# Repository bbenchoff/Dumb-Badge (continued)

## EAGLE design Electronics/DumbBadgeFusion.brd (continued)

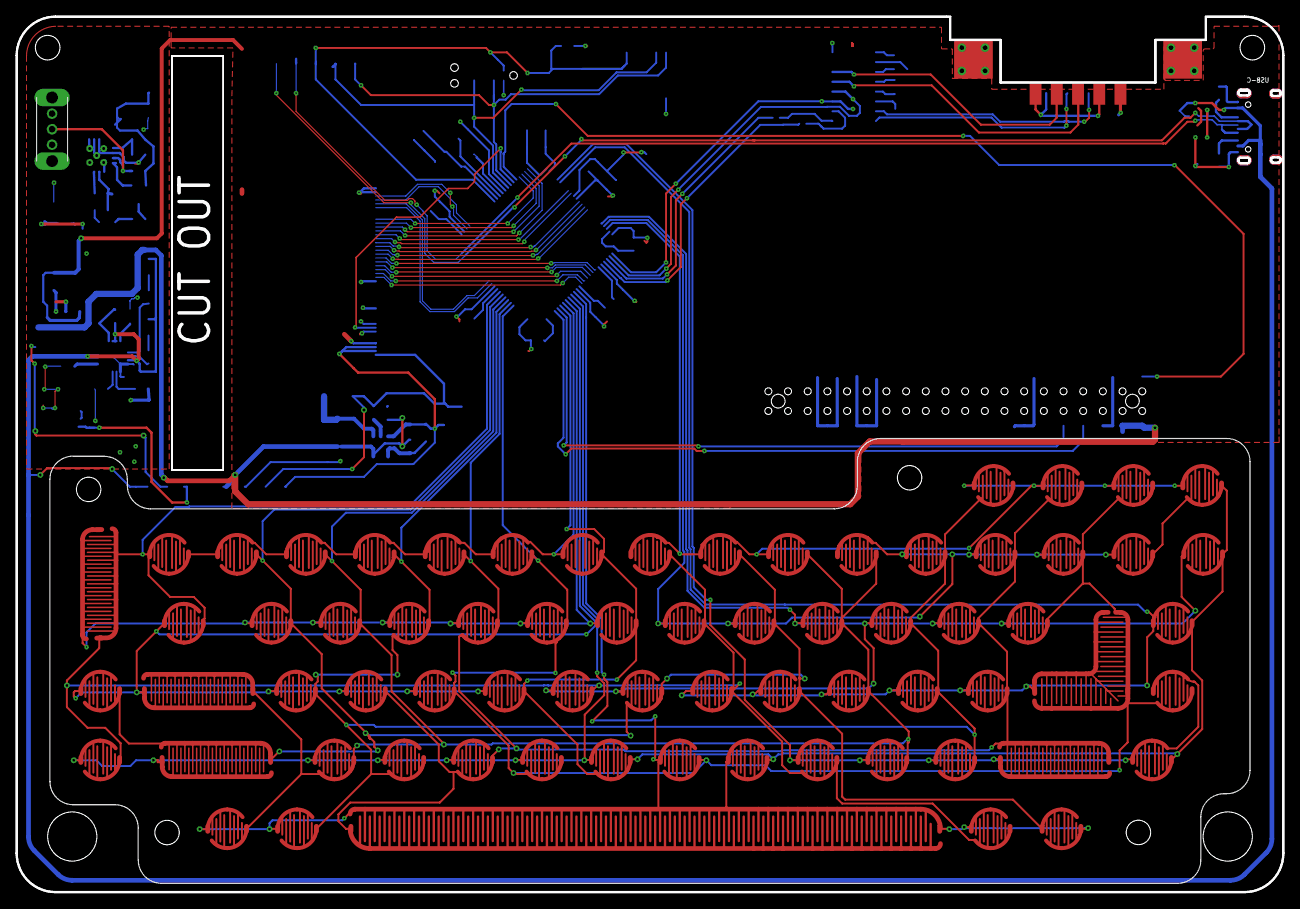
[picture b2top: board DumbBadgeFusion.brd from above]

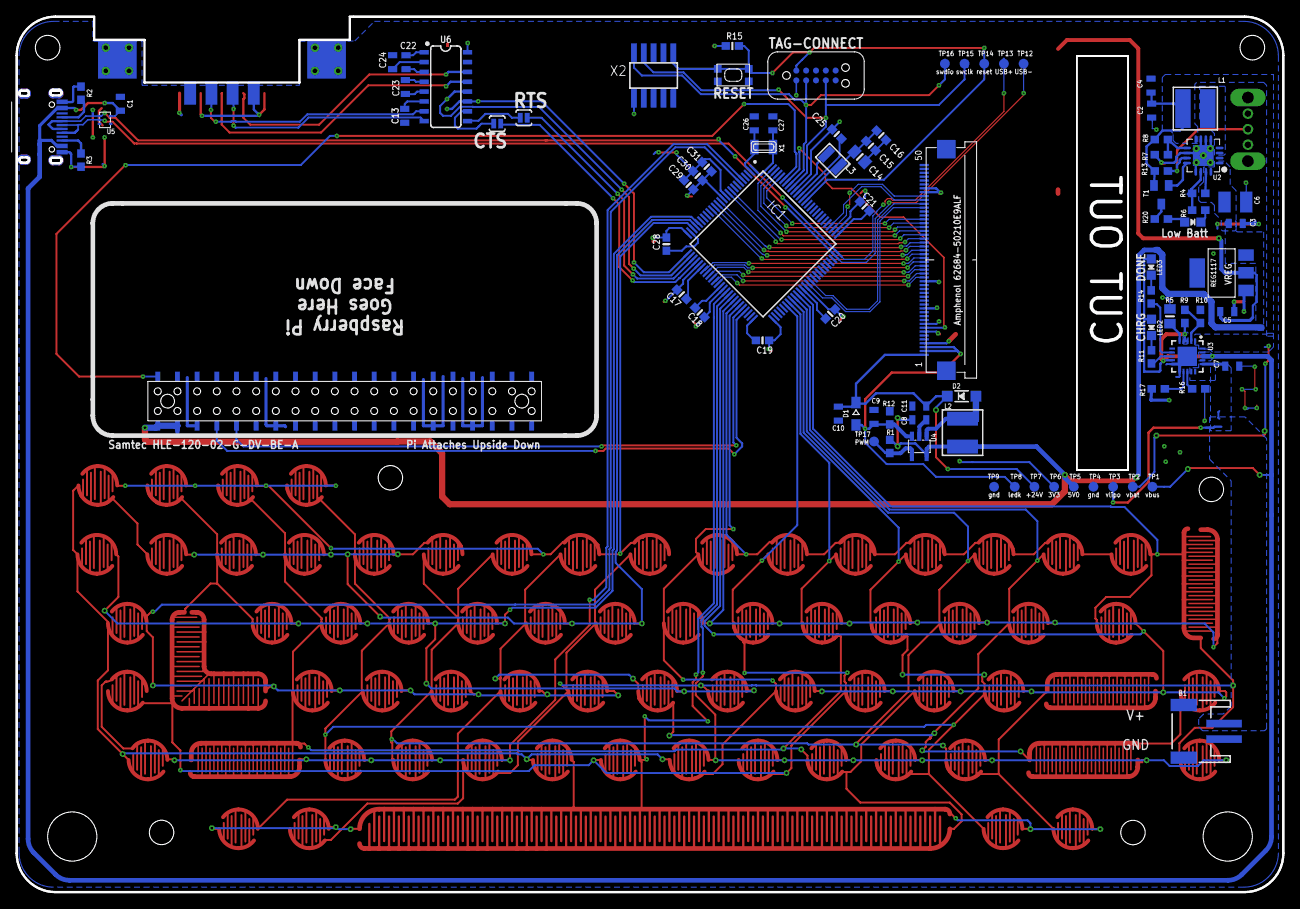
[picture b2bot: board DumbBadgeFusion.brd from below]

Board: 2 copper layers, 163.5 x 113.0 mm, 160 parts (89 on the bottom side), 94 nets.

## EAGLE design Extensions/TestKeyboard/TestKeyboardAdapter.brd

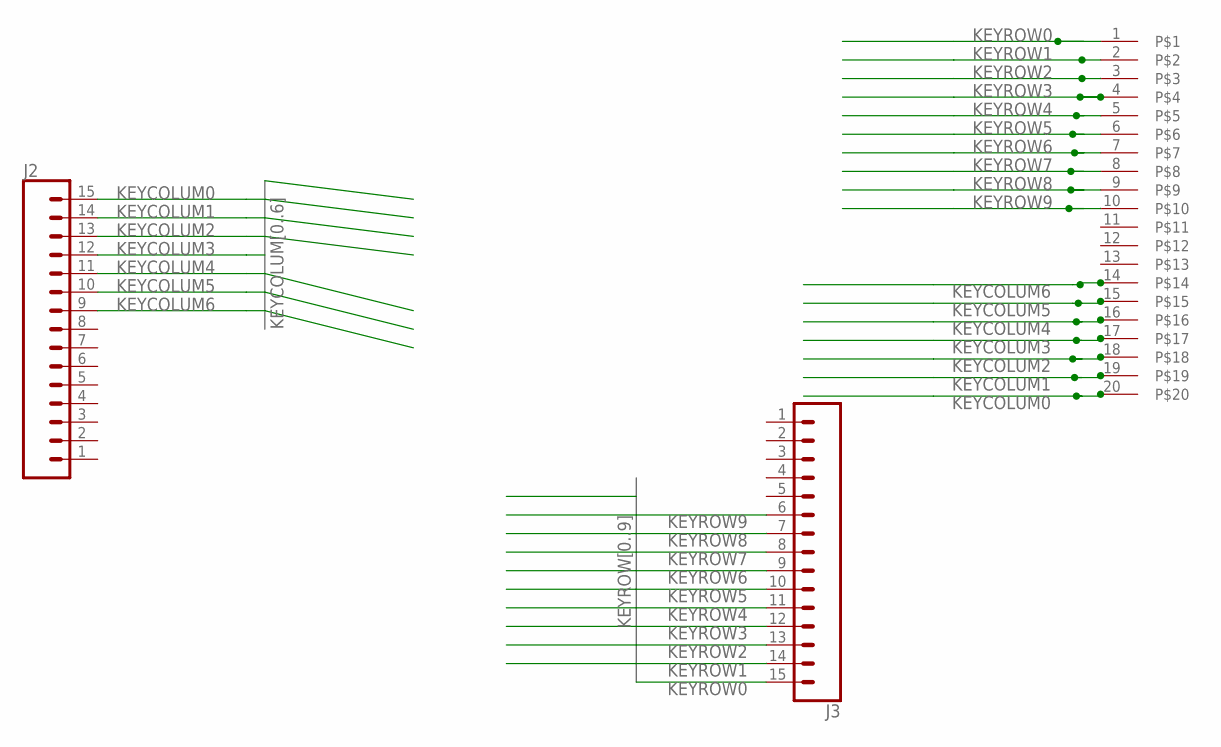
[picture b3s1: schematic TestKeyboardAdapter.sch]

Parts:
J2, J3: CONN_15; 1X15
U$1: FC1-20-L2-T-WT20PIN; FC1-20-L2-T-WT

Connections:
KEYCOLUM0: J2.15, U$1.20
KEYCOLUM1: J2.14, U$1.19
KEYCOLUM2: J2.13, U$1.18
KEYCOLUM3: J2.12, U$1.17
KEYCOLUM4: J2.11, U$1.16
KEYCOLUM5: J2.10, U$1.15
KEYCOLUM6: J2.9, U$1.14
KEYROW0: J3.15, U$1.1
KEYROW1: J3.14, U$1.2
KEYROW2: J3.13, U$1.3
KEYROW3: J3.12, U$1.4
KEYROW4: J3.11, U$1.5
KEYROW5: J3.10, U$1.6
KEYROW6: J3.9, U$1.7
KEYROW7: J3.8, U$1.8
KEYROW8: J3.7, U$1.9
KEYROW9: J3.6, U$1.10

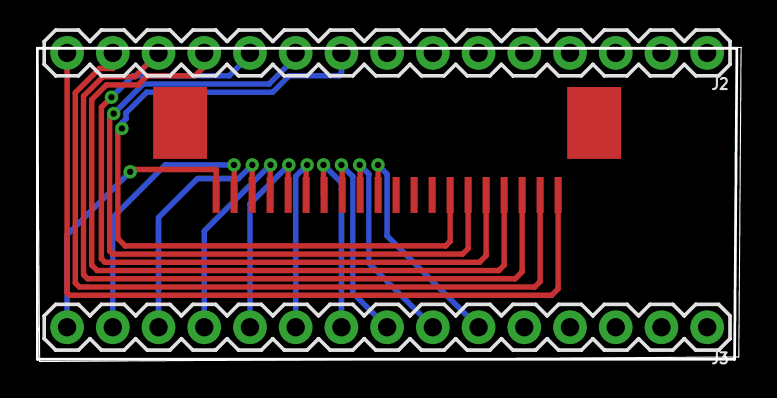
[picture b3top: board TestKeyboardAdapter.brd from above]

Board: 2 copper layers, 39.1 x 17.4 mm, 3 parts (0 on the bottom side), 17 nets.

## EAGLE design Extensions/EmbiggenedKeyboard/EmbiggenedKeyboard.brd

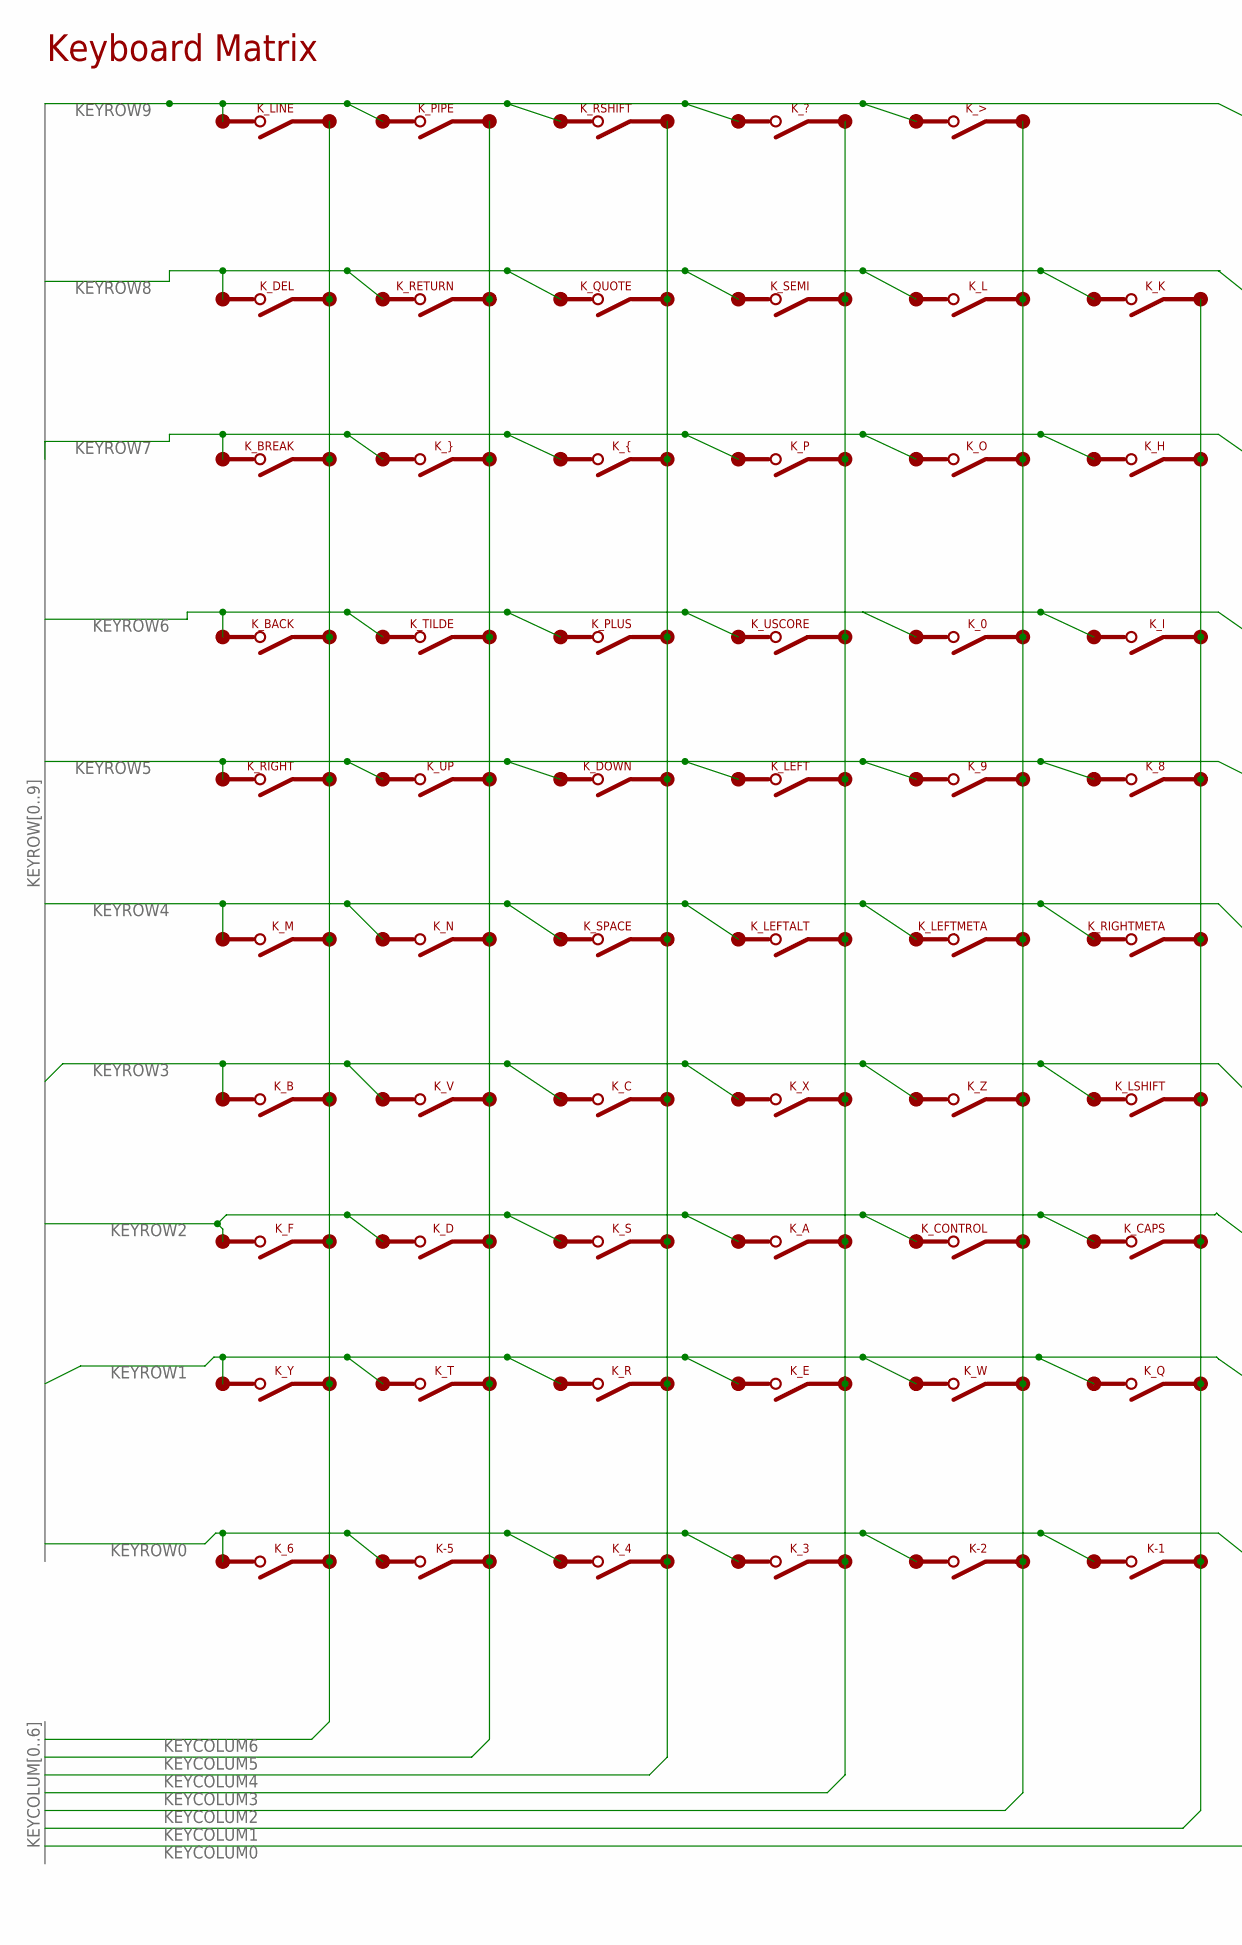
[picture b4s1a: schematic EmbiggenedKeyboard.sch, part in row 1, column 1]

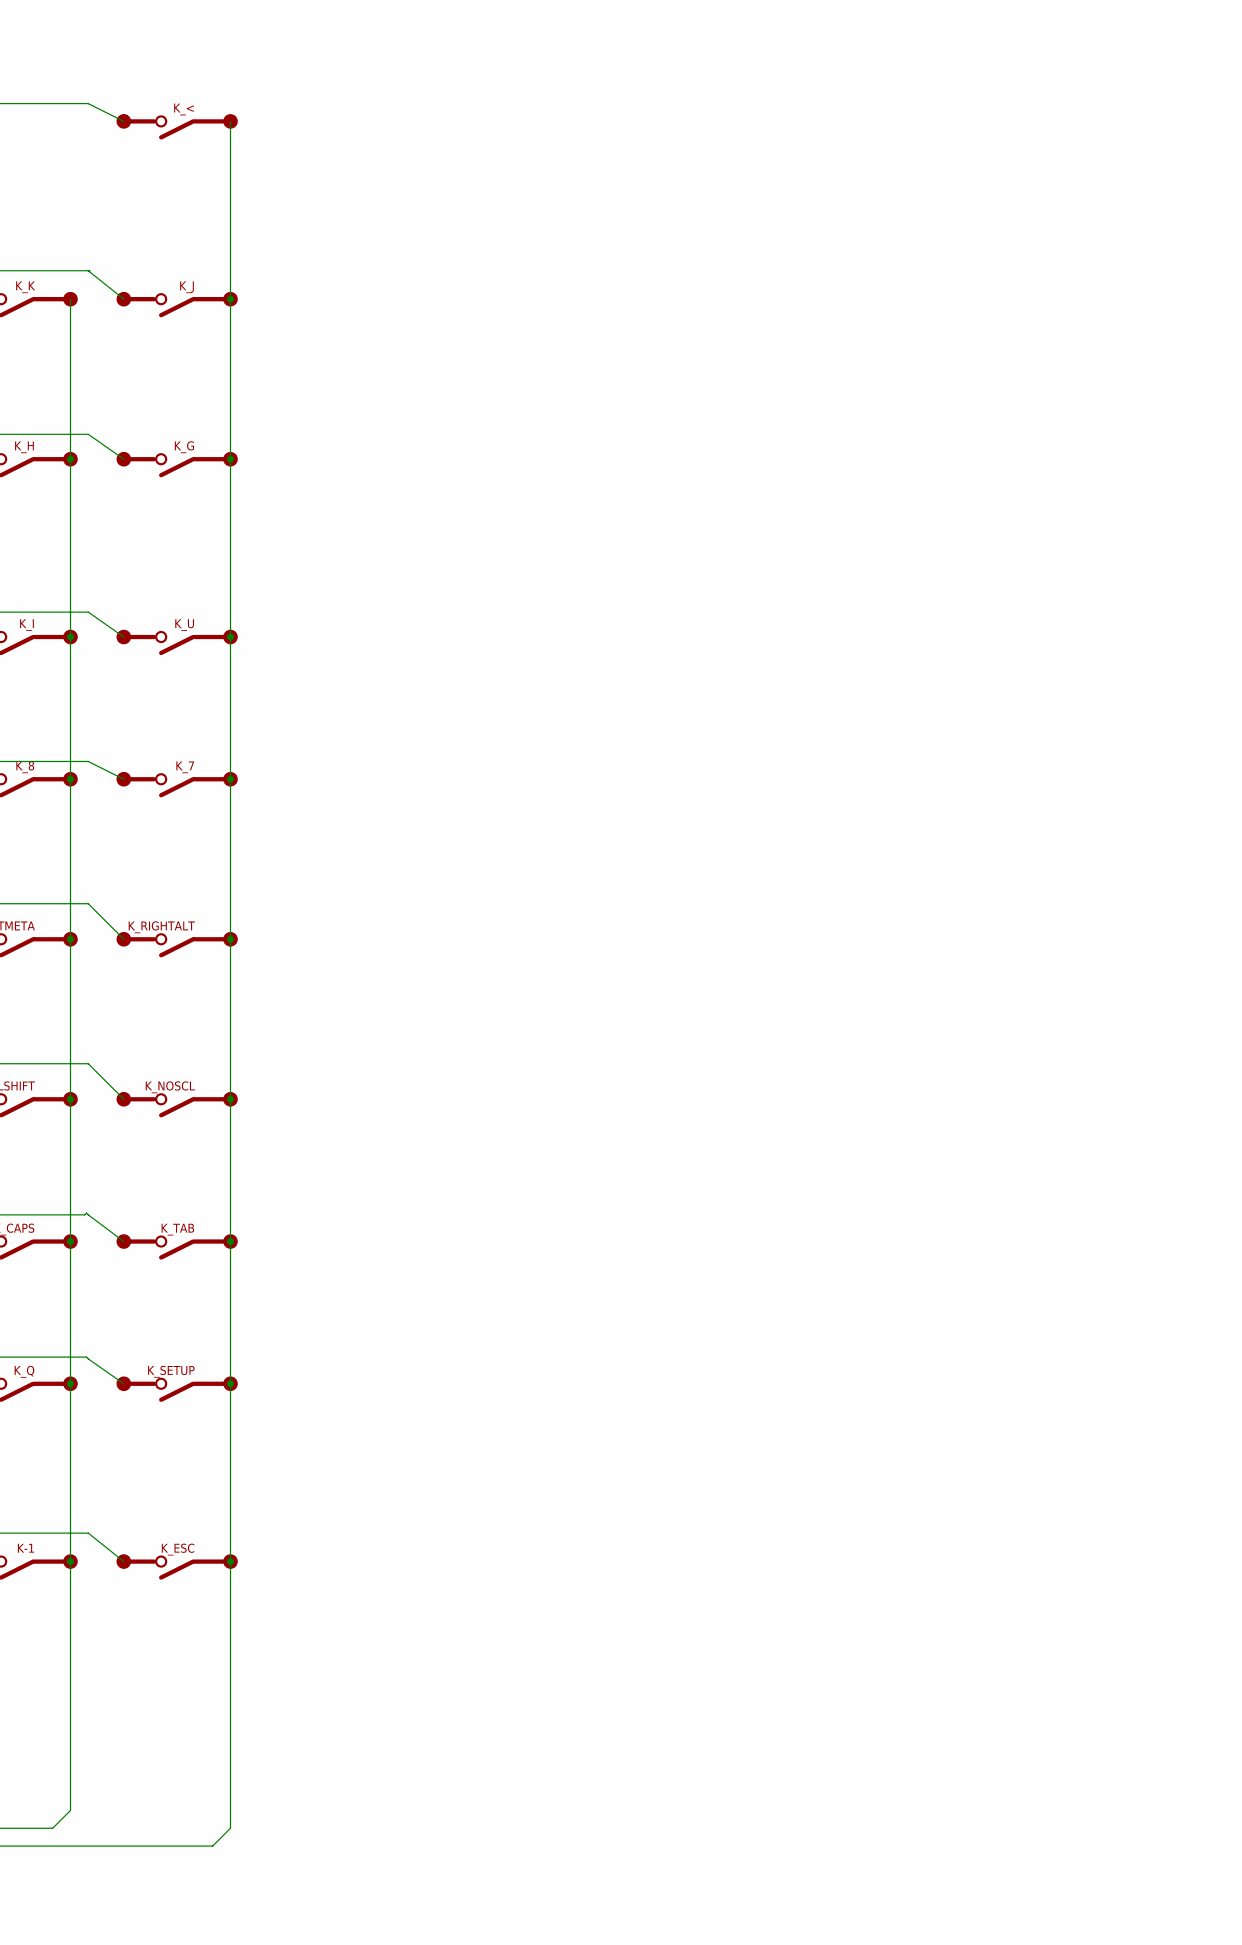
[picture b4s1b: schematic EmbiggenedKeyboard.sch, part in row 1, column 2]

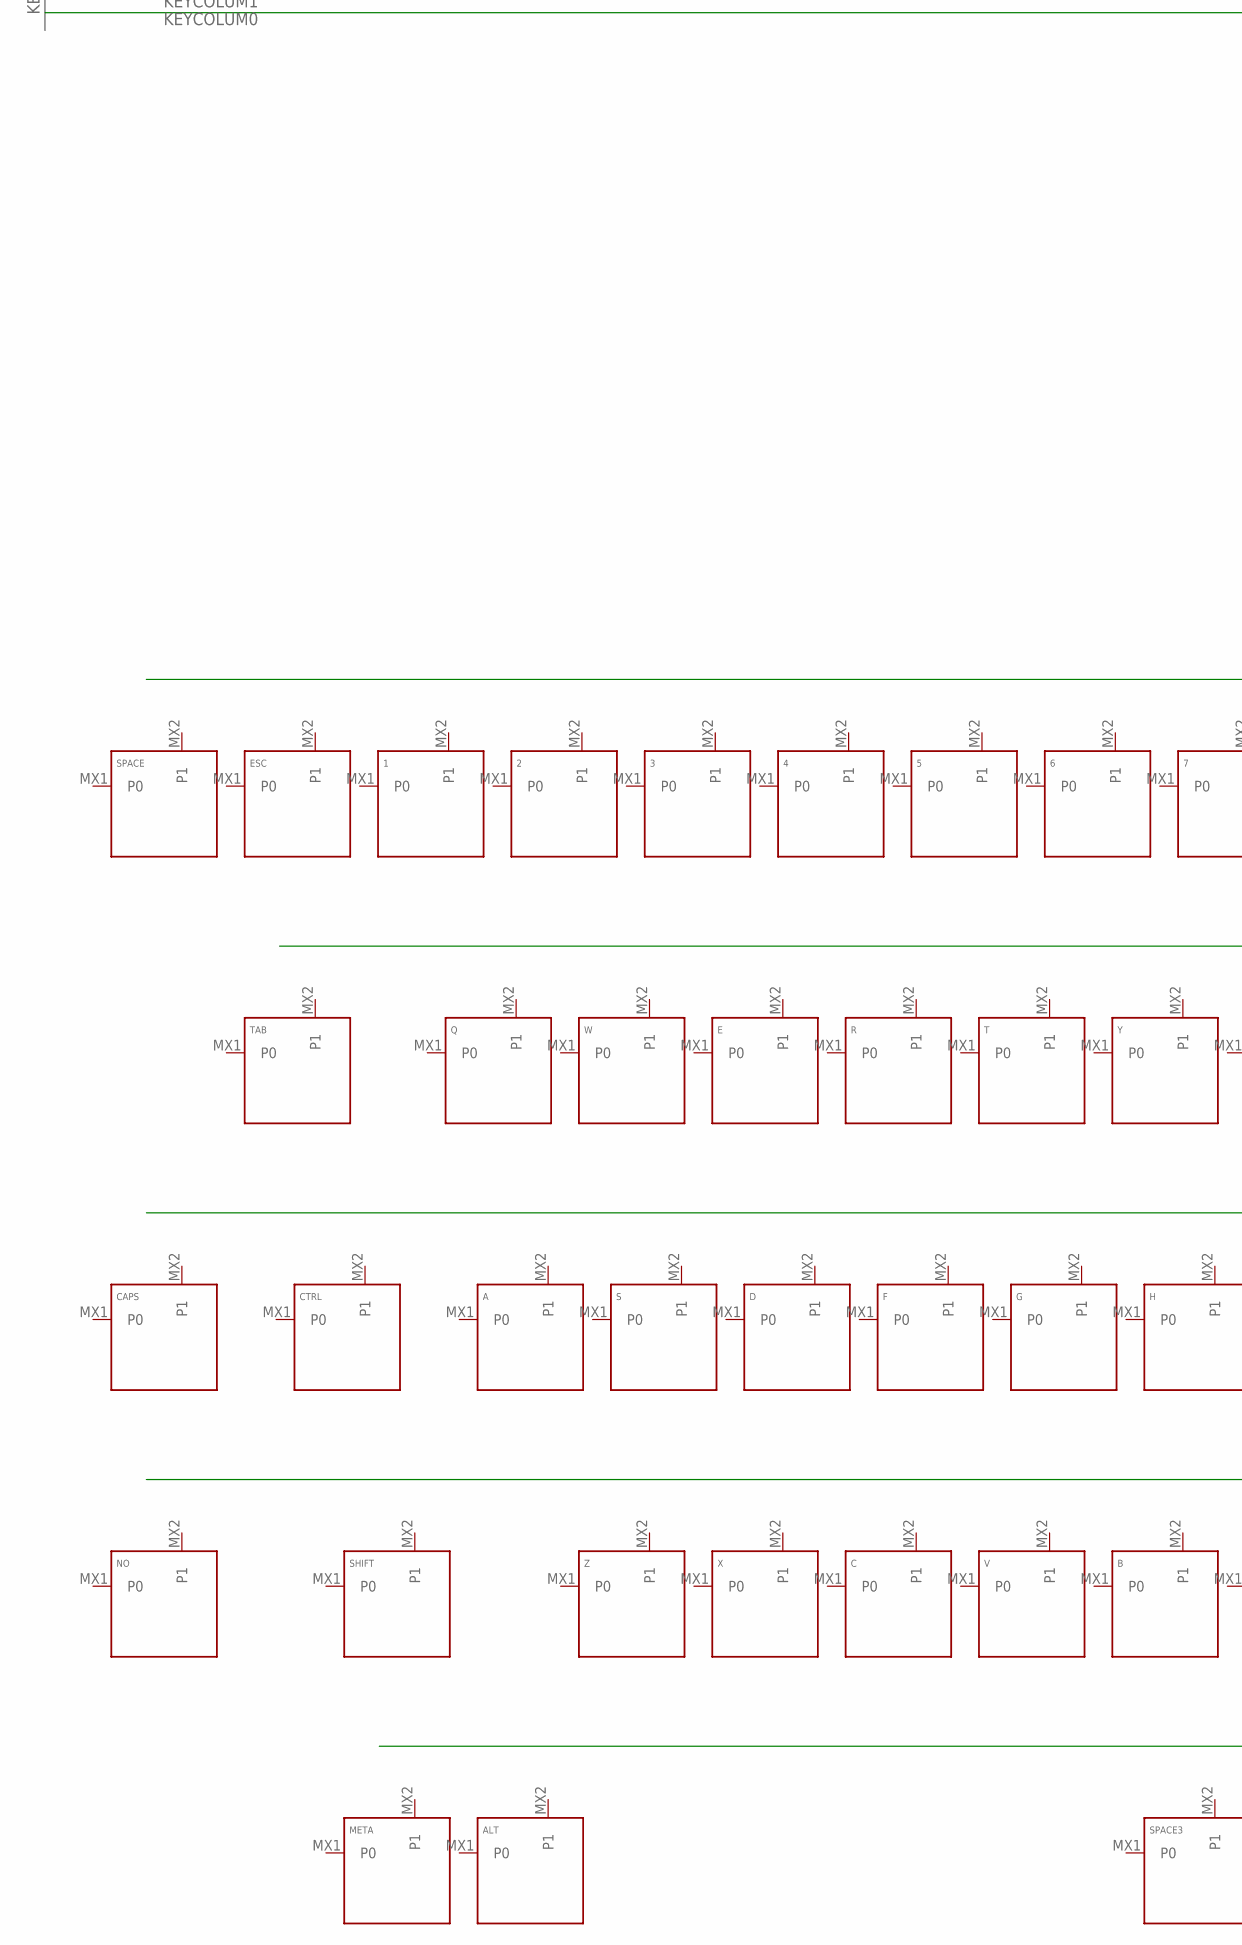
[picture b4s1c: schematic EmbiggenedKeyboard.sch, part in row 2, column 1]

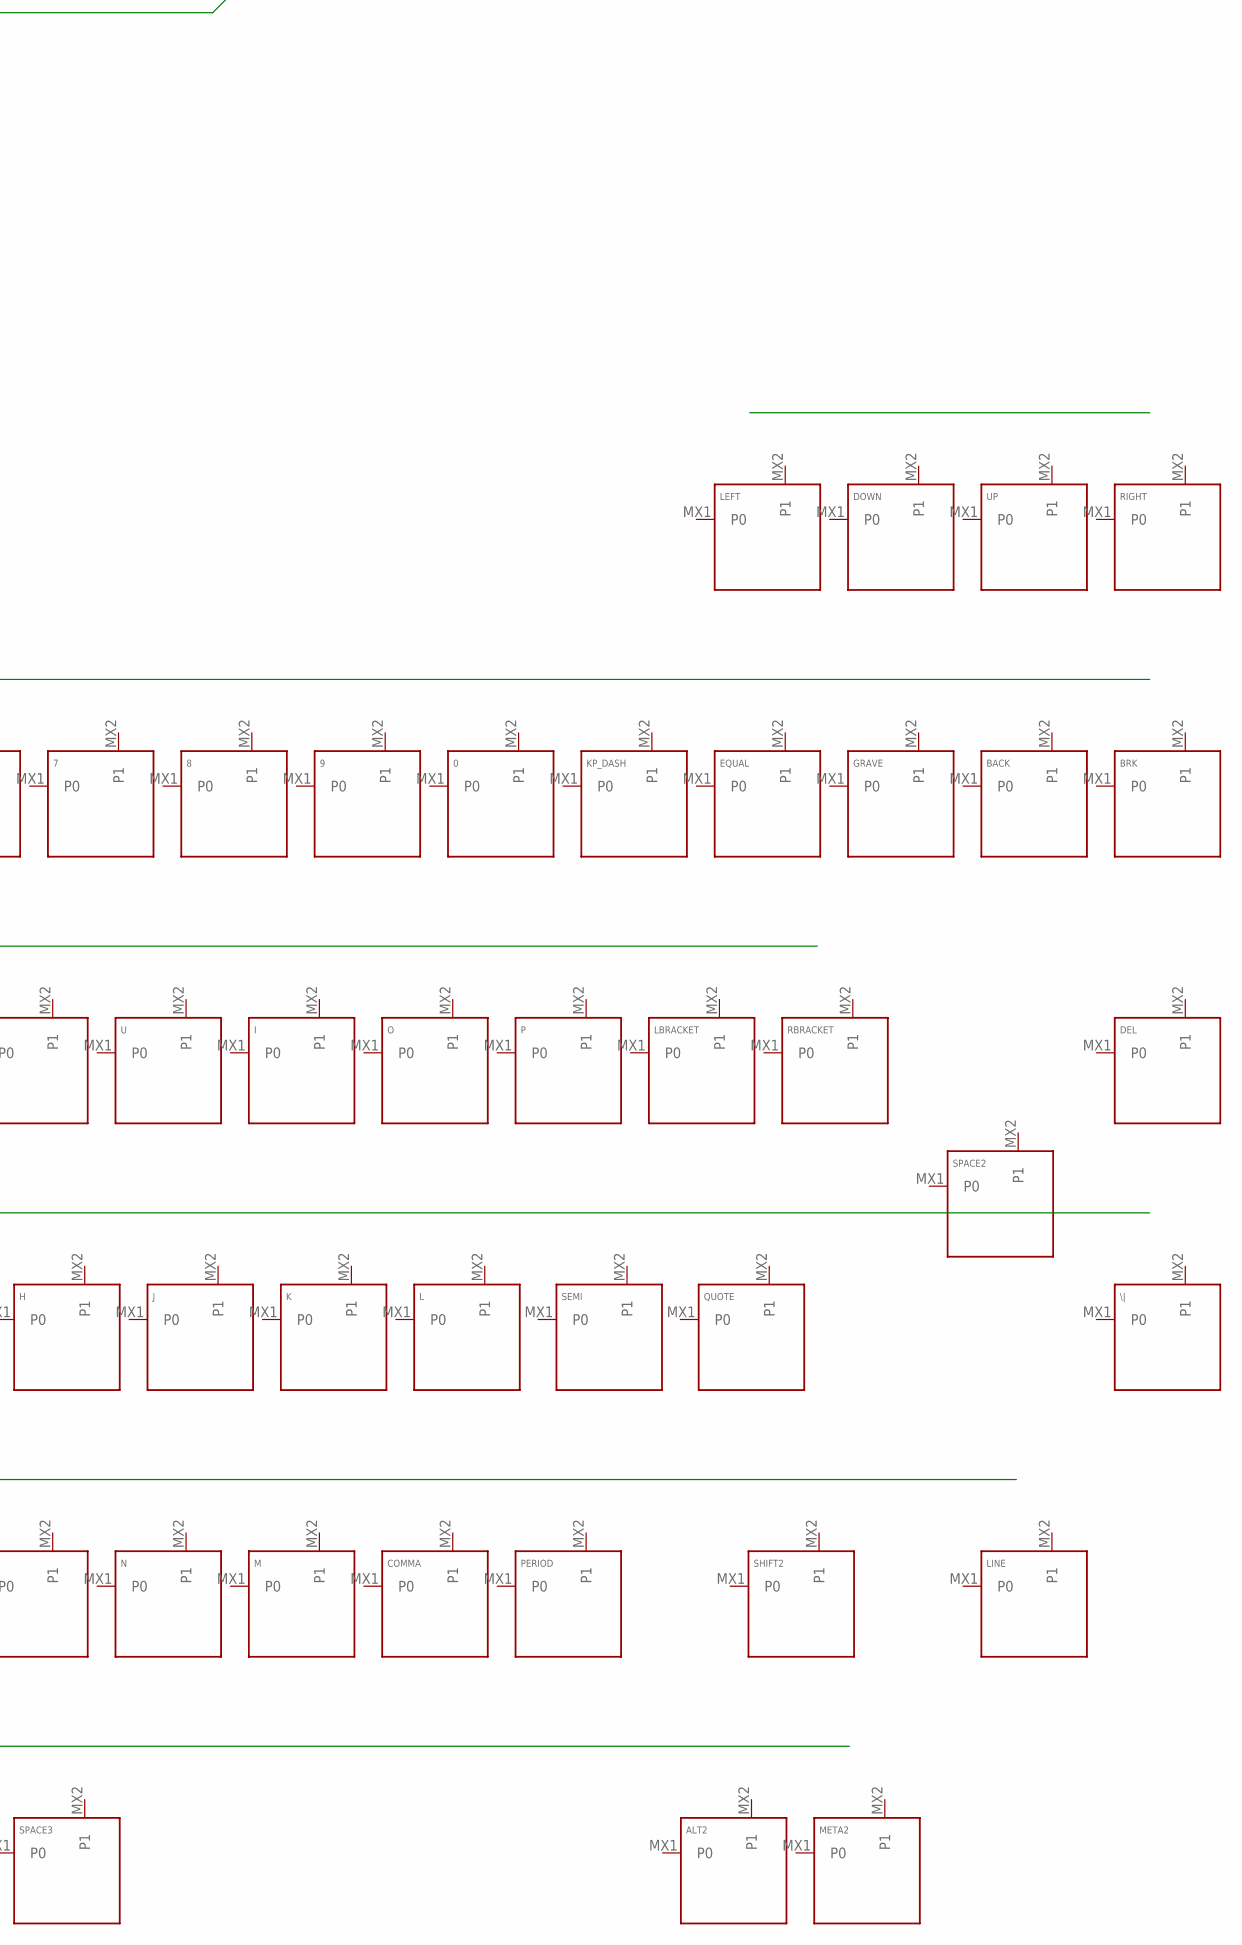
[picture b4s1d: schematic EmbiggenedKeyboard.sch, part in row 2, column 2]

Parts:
0, 1, 2, 3, 4, 5, 6, 7, 8, 9: KEYSWITCH-PLAIN-MX-1U; MX-1U
A: KEYSWITCH-PLAIN-MX-1U; MX-1U
ALT, ALT2: KEYSWITCH-PLAIN-MX-1U; MX-1U
B: KEYSWITCH-PLAIN-MX-1U; MX-1U
BACK: KEYSWITCH-PLAIN-MX-1U; MX-1U
BRK: KEYSWITCH-PLAIN-MX-1U; MX-1U
C: KEYSWITCH-PLAIN-MX-1U; MX-1U
CAPS: KEYSWITCH-PLAIN-MX-1U; MX-1U
COMMA: KEYSWITCH-PLAIN-MX-1U; MX-1U
CTRL: KEYSWITCH-PLAIN-MX-1U; MX-1U
D: KEYSWITCH-PLAIN-MX-1U; MX-1U
DEL: KEYSWITCH-PLAIN-MX-1U; MX-1U
DOWN: KEYSWITCH-PLAIN-MX-1U; MX-1U
E: KEYSWITCH-PLAIN-MX-1U; MX-1U
EQUAL: KEYSWITCH-PLAIN-MX-1U; MX-1U
ESC: KEYSWITCH-PLAIN-MX-1U; MX-1U
F: KEYSWITCH-PLAIN-MX-1U; MX-1U
G: KEYSWITCH-PLAIN-MX-1U; MX-1U
GRAVE: KEYSWITCH-PLAIN-MX-1U; MX-1U
H: KEYSWITCH-PLAIN-MX-1U; MX-1U
I: KEYSWITCH-PLAIN-MX-1U; MX-1U
J: KEYSWITCH-PLAIN-MX-1U; MX-1U
K: KEYSWITCH-PLAIN-MX-1U; MX-1U
K-1, K-2, K-5: 1U_PAD; SILICONE_SWITCH
KP_DASH: KEYSWITCH-PLAIN-MX-1U; MX-1U
K_0, K_3, K_4, K_6, K_7, K_8, K_9: 1U_PAD; SILICONE_SWITCH
K_<: 1U_PAD; SILICONE_SWITCH
K_>: 1U_PAD; SILICONE_SWITCH
K_?: 1U_PAD; SILICONE_SWITCH
K_A: 1U_PAD; SILICONE_SWITCH
K_B: 1U_PAD; SILICONE_SWITCH
K_BACK: 1U_PAD; SILICONE_SWITCH
K_BREAK: 1U_PAD; SILICONE_SWITCH
K_C: 1U_PAD; SILICONE_SWITCH
K_CAPS: 1U_PAD; SILICONE_SWITCH
K_CONTROL: 2U_PAD; SILICONE_SWITCH_2U
K_D: 1U_PAD; SILICONE_SWITCH
K_DEL: 1U_PAD; SILICONE_SWITCH
K_DOWN: 1U_PAD; SILICONE_SWITCH
K_E: 1U_PAD; SILICONE_SWITCH
K_ESC: 1U_PAD; SILICONE_SWITCH
K_F: 1U_PAD; SILICONE_SWITCH
K_G: 1U_PAD; SILICONE_SWITCH
K_H: 1U_PAD; SILICONE_SWITCH
K_I: 1U_PAD; SILICONE_SWITCH
K_J: 1U_PAD; SILICONE_SWITCH
K_K: 1U_PAD; SILICONE_SWITCH
K_L: 1U_PAD; SILICONE_SWITCH
K_LEFT: 1U_PAD; SILICONE_SWITCH
K_LEFTALT: 1U_PAD; SILICONE_SWITCH
K_LEFTMETA: 1U_PAD; SILICONE_SWITCH
K_LINE: 1U_PAD; SILICONE_SWITCH
K_LSHIFT: 2U_PAD; SILICONE_SWITCH_2U
K_M: 1U_PAD; SILICONE_SWITCH
K_N: 1U_PAD; SILICONE_SWITCH
K_NOSCL: 1U_PAD; SILICONE_SWITCH
K_O: 1U_PAD; SILICONE_SWITCH
K_P: 1U_PAD; SILICONE_SWITCH
K_PIPE: 1U_PAD; SILICONE_SWITCH
K_PLUS: 1U_PAD; SILICONE_SWITCH
K_Q: 1U_PAD; SILICONE_SWITCH
K_QUOTE: 1U_PAD; SILICONE_SWITCH
K_R: 1U_PAD; SILICONE_SWITCH
K_RETURN: RETURN_PAD; SILICONE_RETURN
K_RIGHT: 1U_PAD; SILICONE_SWITCH
K_RIGHTALT: 1U_PAD; SILICONE_SWITCH
K_RIGHTMETA: 1U_PAD; SILICONE_SWITCH
K_RSHIFT: 2U_PAD; SILICONE_SWITCH_2U
K_S: 1U_PAD; SILICONE_SWITCH
K_SEMI: 1U_PAD; SILICONE_SWITCH
K_SETUP: 2U_PAD; SILICONE_SWITCH_2U
K_SPACE: SPACE_PAD; SILICONE_SPACE
K_T: 1U_PAD; SILICONE_SWITCH
K_TAB: 1U_PAD; SILICONE_SWITCH
K_TILDE: 1U_PAD; SILICONE_SWITCH
K_U: 1U_PAD; SILICONE_SWITCH
K_UP: 1U_PAD; SILICONE_SWITCH
K_USCORE: 1U_PAD; SILICONE_SWITCH
K_V: 1U_PAD; SILICONE_SWITCH
K_W: 1U_PAD; SILICONE_SWITCH
K_X: 1U_PAD; SILICONE_SWITCH
K_Y: 1U_PAD; SILICONE_SWITCH
K_Z: 1U_PAD; SILICONE_SWITCH
K_{: 1U_PAD; SILICONE_SWITCH
K_}: 1U_PAD; SILICONE_SWITCH
L: KEYSWITCH-PLAIN-MX-1U; MX-1U
LBRACKET: KEYSWITCH-PLAIN-MX-1U; MX-1U
LEFT: KEYSWITCH-PLAIN-MX-1U; MX-1U
LINE: KEYSWITCH-PLAIN-MX-1U; MX-1U
M: KEYSWITCH-PLAIN-MX-1U; MX-1U
META, META2: KEYSWITCH-PLAIN-MX-1U; MX-1U
N: KEYSWITCH-PLAIN-MX-1U; MX-1U
NO: KEYSWITCH-PLAIN-MX-1U; MX-1U
O: KEYSWITCH-PLAIN-MX-1U; MX-1U
P: KEYSWITCH-PLAIN-MX-1U; MX-1U
PERIOD: KEYSWITCH-PLAIN-MX-1U; MX-1U
Q: KEYSWITCH-PLAIN-MX-1U; MX-1U
QUOTE: KEYSWITCH-PLAIN-MX-1U; MX-1U
R: KEYSWITCH-PLAIN-MX-1U; MX-1U
RBRACKET: KEYSWITCH-PLAIN-MX-1U; MX-1U
RIGHT: KEYSWITCH-PLAIN-MX-1U; MX-1U
S: KEYSWITCH-PLAIN-MX-1U; MX-1U
SEMI: KEYSWITCH-PLAIN-MX-1U; MX-1U
SHIFT, SHIFT2: KEYSWITCH-PLAIN-MX-1U; MX-1U
SPACE, SPACE2, SPACE3: KEYSWITCH-PLAIN-MX-1U; MX-1U
T: KEYSWITCH-PLAIN-MX-1U; MX-1U
TAB: KEYSWITCH-PLAIN-MX-1U; MX-1U
U: KEYSWITCH-PLAIN-MX-1U; MX-1U
UP: KEYSWITCH-PLAIN-MX-1U; MX-1U
V: KEYSWITCH-PLAIN-MX-1U; MX-1U
W: KEYSWITCH-PLAIN-MX-1U; MX-1U
X: KEYSWITCH-PLAIN-MX-1U; MX-1U
Y: KEYSWITCH-PLAIN-MX-1U; MX-1U
Z: KEYSWITCH-PLAIN-MX-1U; MX-1U
\|: KEYSWITCH-PLAIN-MX-1U; MX-1U

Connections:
KEYCOLUM0: K_7.P$2, K_<.P$2, K_ESC.P$2, K_G.P$2, K_J.P$2, K_NOSCL.P$2, K_RIGHTALT.P$2, K_SETUP.P$2, K_TAB.P$2, K_U.P$2
KEYCOLUM1: K-1.P$2, K_8.P$2, K_CAPS.P$2, K_H.P$2, K_I.P$2, K_K.P$2, K_LSHIFT.P$2, K_Q.P$2, K_RIGHTMETA.P$2
KEYCOLUM2: K-2.P$2, K_0.P$2, K_9.P$2, K_>.P$2, K_CONTROL.P$2, K_L.P$2, K_LEFTMETA.P$2, K_O.P$2, K_W.P$2, K_Z.P$2
KEYCOLUM3: K_3.P$2, K_?.P$2, K_A.P$2, K_E.P$2, K_LEFT.P$2, K_LEFTALT.P$2, K_P.P$2, K_SEMI.P$2, K_USCORE.P$2, K_X.P$2
KEYCOLUM4: K_4.P$2, K_C.P$2, K_DOWN.P$2, K_PLUS.P$2, K_QUOTE.P$2, K_R.P$2, K_RSHIFT.P$2, K_S.P$2, K_SPACE.P$2, K_{.P$2
KEYCOLUM5: K-5.P$2, K_D.P$2, K_N.P$2, K_PIPE.P$2, K_RETURN.P$2, K_T.P$2, K_TILDE.P$2, K_UP.P$2, K_V.P$2, K_}.P$2
KEYCOLUM6: K_6.P$2, K_B.P$2, K_BACK.P$2, K_BREAK.P$2, K_DEL.P$2, K_F.P$2, K_LINE.P$2, K_M.P$2, K_RIGHT.P$2, K_Y.P$2
KEYROW0: K-1.P$1, K-2.P$1, K-5.P$1, K_3.P$1, K_4.P$1, K_6.P$1, K_ESC.P$1
KEYROW1: K_E.P$1, K_Q.P$1, K_R.P$1, K_SETUP.P$1, K_T.P$1, K_W.P$1, K_Y.P$1
KEYROW2: K_A.P$1, K_CAPS.P$1, K_CONTROL.P$1, K_D.P$1, K_F.P$1, K_S.P$1, K_TAB.P$1
KEYROW3: K_B.P$1, K_C.P$1, K_LSHIFT.P$1, K_NOSCL.P$1, K_V.P$1, K_X.P$1, K_Z.P$1
KEYROW4: K_LEFTALT.P$1, K_LEFTMETA.P$1, K_M.P$1, K_N.P$1, K_RIGHTALT.P$1, K_RIGHTMETA.P$1, K_SPACE.P$1
KEYROW5: K_7.P$1, K_8.P$1, K_9.P$1, K_DOWN.P$1, K_LEFT.P$1, K_RIGHT.P$1, K_UP.P$1
KEYROW6: K_0.P$1, K_BACK.P$1, K_I.P$1, K_PLUS.P$1, K_TILDE.P$1, K_U.P$1, K_USCORE.P$1
KEYROW7: K_BREAK.P$1, K_G.P$1, K_H.P$1, K_O.P$1, K_P.P$1, K_{.P$1, K_}.P$1
KEYROW8: K_DEL.P$1, K_J.P$1, K_K.P$1, K_L.P$1, K_QUOTE.P$1, K_RETURN.P$1, K_SEMI.P$1
KEYROW9: K_<.P$1, K_>.P$1, K_?.P$1, K_LINE.P$1, K_PIPE.P$1, K_RSHIFT.P$1

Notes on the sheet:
Keyboard Matrix

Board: 2 copper layers, 137 parts (0 on the bottom side), 17 nets, no tracks yet.

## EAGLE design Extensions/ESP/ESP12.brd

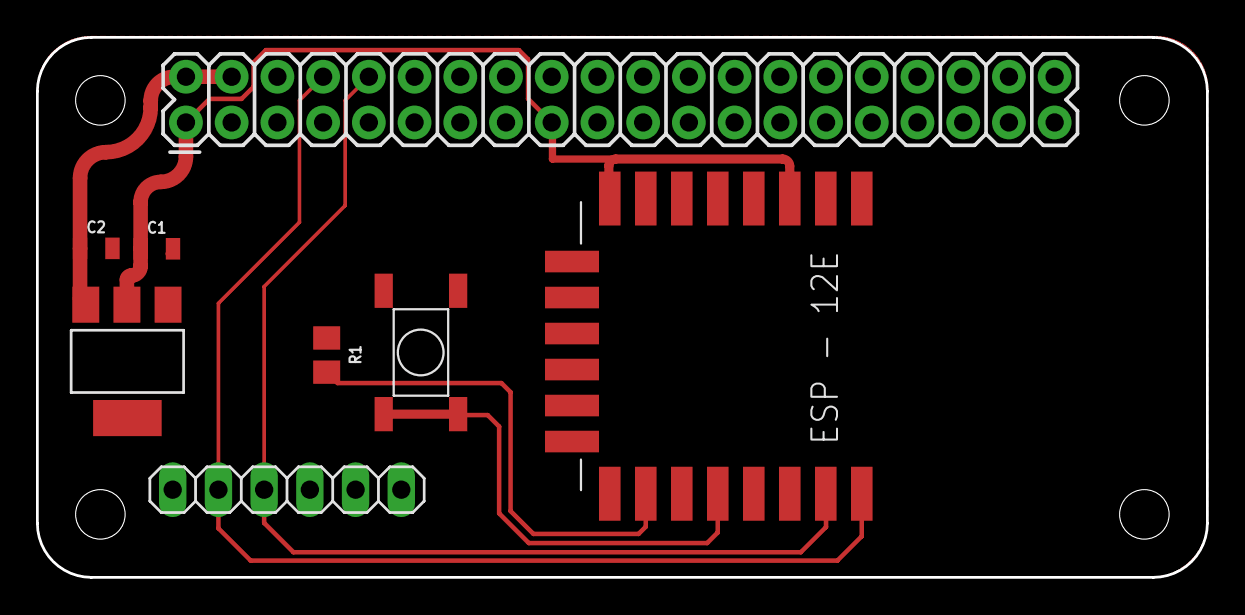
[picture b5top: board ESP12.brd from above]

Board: 2 copper layers, 65.0 x 30.0 mm, 8 parts (0 on the bottom side), 7 nets.

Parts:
C1, C2: 10uF; 0805
FLASH: MOMENTARYSW; SWITCHMOMENTARY
IC1: REG1117; SOT223
J1: RASPBERRYPI-40-PIN-GPIO_PTH_NO_SHROUD; 2X20
JP2: 1X06
R1: 10k; R0805
U3: ESP12E-SMD

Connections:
5V: C2.1, IC1.3, J1.2, J1.4
FTDI_RX: J1.8, JP2.5, U3.TXD0
FTDI_TX: J1.10, JP2.4, U3.RXD0
GND: C1.2, C2.2, FLASH.R1, FLASH.R2, IC1.1, J1.6, J1.9, J1.14, J1.20, J1.25, J1.30, J1.34, J1.39, JP2.1, R1.1, U3.GND
unnamed: R1.2, U3.GPIO15
unnamed: FLASH.L1, FLASH.L2, U3.GPIO0
VCC: C1.1, IC1.2, J1.1, J1.17, U3.CH_PD, U3.VCC

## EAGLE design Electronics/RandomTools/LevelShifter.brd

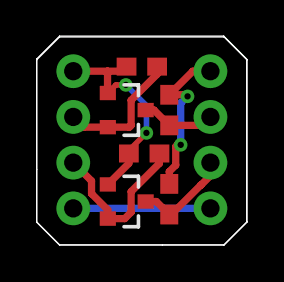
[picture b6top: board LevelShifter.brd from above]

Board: 2 copper layers, 11.7 x 11.6 mm, 8 parts (0 on the bottom side), 7 nets.

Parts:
J1, J2: 1X04_NO_SILK
Q1, Q2: 220mA/50V/3.5Ω; SOT23-3
R1, R2, R3, R4: 10k; 0603

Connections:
GND: J1.1, J2.4
HI1: J2.2, Q1.3, R3.1
HI2: J2.3, Q2.3, R4.1
HIPW: J2.1, R3.2, R4.2
LOW1: J1.3, Q1.2, R1.1
LOW2: J1.2, Q2.2, R2.1
LOWPW: J1.4, Q1.1, Q2.1, R1.2, R2.2

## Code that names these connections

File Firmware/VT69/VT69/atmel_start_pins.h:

/*
 * Code generated from Atmel Start.
 *
 * This file will be overwritten when reconfiguring your Atmel Start project.
 * Please copy examples or other code you want to keep to a separate file
 * to avoid losing it when reconfiguring.
 */
#ifndef ATMEL_START_PINS_H_INCLUDED
#define ATMEL_START_PINS_H_INCLUDED


// SAMD51 has 14 pin functions

#define GPIO_PIN_FUNCTION_A 0
#define GPIO_PIN_FUNCTION_B 1
#define GPIO_PIN_FUNCTION_C 2
#define GPIO_PIN_FUNCTION_D 3
#define GPIO_PIN_FUNCTION_E 4
#define GPIO_PIN_FUNCTION_F 5
#define GPIO_PIN_FUNCTION_G 6
#define GPIO_PIN_FUNCTION_H 7
#define GPIO_PIN_FUNCTION_I 8
#define GPIO_PIN_FUNCTION_J 9
#define GPIO_PIN_FUNCTION_K 10
#define GPIO_PIN_FUNCTION_L 11
#define GPIO_PIN_FUNCTION_M 12
#define GPIO_PIN_FUNCTION_N 13

#define PA00 GPIO(GPIO_PORTA, 0)
#define PA01 GPIO(GPIO_PORTA, 1)
#define PA02 GPIO(GPIO_PORTA, 2)
#define PA03 GPIO(GPIO_PORTA, 3)
#define PA04 GPIO(GPIO_PORTA, 4)
#define PA05 GPIO(GPIO_PORTA, 5)
#define PA06 GPIO(GPIO_PORTA, 6)
#define PA07 GPIO(GPIO_PORTA, 7)
#define PA08 GPIO(GPIO_PORTA, 8)
#define PA09 GPIO(GPIO_PORTA, 9)
#define PA10 GPIO(GPIO_PORTA, 10)
#define PA11 GPIO(GPIO_PORTA, 11)
#define PA12 GPIO(GPIO_PORTA, 12)
#define PA13 GPIO(GPIO_PORTA, 13)
#define PA14 GPIO(GPIO_PORTA, 14)
#define PA15 GPIO(GPIO_PORTA, 15)
#define PA16 GPIO(GPIO_PORTA, 16)
#define PA17 GPIO(GPIO_PORTA, 17)
#define PA18 GPIO(GPIO_PORTA, 18)
#define PA19 GPIO(GPIO_PORTA, 19)
#define PA20 GPIO(GPIO_PORTA, 20)
#define PA21 GPIO(GPIO_PORTA, 21)
#define PA22 GPIO(GPIO_PORTA, 22)
#define PA23 GPIO(GPIO_PORTA, 23)
#define PA24 GPIO(GPIO_PORTA, 24)
#define PA25 GPIO(GPIO_PORTA, 25)
#define PA27 GPIO(GPIO_PORTA, 27)
#define PA30 GPIO(GPIO_PORTA, 30)
#define PA31 GPIO(GPIO_PORTA, 31)

#define PB00 GPIO(GPIO_PORTB, 0)
#define PB01 GPIO(GPIO_PORTB, 1)
#define PB02 GPIO(GPIO_PORTB, 2)
#define PB03 GPIO(GPIO_PORTB, 3)
#define PB04 GPIO(GPIO_PORTB, 4)
#define PB05 GPIO(GPIO_PORTB, 5)
#define PB06 GPIO(GPIO_PORTB, 6)
#define PB07 GPIO(GPIO_PORTB, 7)
#define PB08 GPIO(GPIO_PORTB, 8)
#define PB09 GPIO(GPIO_PORTB, 9)
#define PB10 GPIO(GPIO_PORTB, 10)
#define PB11 GPIO(GPIO_PORTB, 11)
#define PB12 GPIO(GPIO_PORTB, 12)
#define PB13 GPIO(GPIO_PORTB, 13)
#define PB14 GPIO(GPIO_PORTB, 14)
#define PB15 GPIO(GPIO_PORTB, 15)
#define PB16 GPIO(GPIO_PORTB, 16)
#define PB17 GPIO(GPIO_PORTB, 17)
#define PB18 GPIO(GPIO_PORTB, 18)
#define PB19 GPIO(GPIO_PORTB, 19)
#define PB20 GPIO(GPIO_PORTB, 20)
#define PB21 GPIO(GPIO_PORTB, 21)
#define PB22 GPIO(GPIO_PORTB, 22)
#define PB23 GPIO(GPIO_PORTB, 23)
#define PB24 GPIO(GPIO_PORTB, 24)
#define PB25 GPIO(GPIO_PORTB, 25)
#define PB30 GPIO(GPIO_PORTB, 30)
#define PB31 GPIO(GPIO_PORTB, 31)

#define PC00 GPIO(GPIO_PORTC, 0)
#define PC01 GPIO(GPIO_PORTC, 1)
#define PC02 GPIO(GPIO_PORTC, 2)
#define PC03 GPIO(GPIO_PORTC, 3)
#define PC05 GPIO(GPIO_PORTC, 5)
#define PC06 GPIO(GPIO_PORTC, 6)
#define PC07 GPIO(GPIO_PORTC, 7)
#define PC10 GPIO(GPIO_PORTC, 10)
#define PC11 GPIO(GPIO_PORTC, 11)
#define PC12 GPIO(GPIO_PORTC, 12)
#define PC13 GPIO(GPIO_PORTC, 13)
#define PC14 GPIO(GPIO_PORTC, 14)
#define PC15 GPIO(GPIO_PORTC, 15)
#define PC16 GPIO(GPIO_PORTC, 16)
#define PC17 GPIO(GPIO_PORTC, 17)
#define PC18 GPIO(GPIO_PORTC, 18)
#define PC19 GPIO(GPIO_PORTC, 19)
#define PC20 GPIO(GPIO_PORTC, 20)
#define PC21 GPIO(GPIO_PORTC, 21)
#define PC24 GPIO(GPIO_PORTC, 24)
#define PC25 GPIO(GPIO_PORTC, 25)
#define PC26 GPIO(GPIO_PORTC, 26)
#define PC27 GPIO(GPIO_PORTC, 27)
#define PC28 GPIO(GPIO_PORTC, 28)

#endif // ATMEL_START_PINS_H_INCLUDED

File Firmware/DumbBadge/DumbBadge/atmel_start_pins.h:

/*
 * Code generated from Atmel Start.
 *
 * This file will be overwritten when reconfiguring your Atmel Start project.
 * Please copy examples or other code you want to keep to a separate file
 * to avoid losing it when reconfiguring.
 */
#ifndef ATMEL_START_PINS_H_INCLUDED
#define ATMEL_START_PINS_H_INCLUDED

#include <hal_gpio.h>

// SAMD21 has 8 pin functions

#define GPIO_PIN_FUNCTION_A 0
#define GPIO_PIN_FUNCTION_B 1
#define GPIO_PIN_FUNCTION_C 2
#define GPIO_PIN_FUNCTION_D 3
#define GPIO_PIN_FUNCTION_E 4
#define GPIO_PIN_FUNCTION_F 5
#define GPIO_PIN_FUNCTION_G 6
#define GPIO_PIN_FUNCTION_H 7

#define Crystal1 GPIO(GPIO_PORTA, 0)
#define Crystal2 GPIO(GPIO_PORTA, 1)
#define PA04 GPIO(GPIO_PORTA, 4)
#define PA05 GPIO(GPIO_PORTA, 5)
#define PA08 GPIO(GPIO_PORTA, 8)
#define PA09 GPIO(GPIO_PORTA, 9)
#define PA24 GPIO(GPIO_PORTA, 24)
#define PA25 GPIO(GPIO_PORTA, 25)
#define LCD_Data_00 GPIO(GPIO_PORTB, 0)
#define LCD_Data_01 GPIO(GPIO_PORTB, 1)
#define LCD_Data_02 GPIO(GPIO_PORTB, 2)
#define LCD_Data_03 GPIO(GPIO_PORTB, 3)
#define LCD_Data_04 GPIO(GPIO_PORTB, 4)
#define LCD_Data_05 GPIO(GPIO_PORTB, 5)
#define LCD_Data_06 GPIO(GPIO_PORTB, 6)
#define LCD_Data_07 GPIO(GPIO_PORTB, 7)
#define LCD_Data_08 GPIO(GPIO_PORTB, 8)
#define LCD_Data_09 GPIO(GPIO_PORTB, 9)
#define LCD_Data_10 GPIO(GPIO_PORTB, 10)
#define LCD_Data_11 GPIO(GPIO_PORTB, 11)
#define LCD_Data_12 GPIO(GPIO_PORTB, 12)
#define LCD_Data_13 GPIO(GPIO_PORTB, 13)
#define LCD_Data_14 GPIO(GPIO_PORTB, 14)
#define LCD_Data_15 GPIO(GPIO_PORTB, 15)
#define LCD_RD GPIO(GPIO_PORTB, 16)
#define LCD_WR GPIO(GPIO_PORTB, 17)
#define LCD_CS GPIO(GPIO_PORTB, 22)
#define LCD_DC GPIO(GPIO_PORTB, 23)
#define LCD_RST GPIO(GPIO_PORTB, 30)

#endif // ATMEL_START_PINS_H_INCLUDED
